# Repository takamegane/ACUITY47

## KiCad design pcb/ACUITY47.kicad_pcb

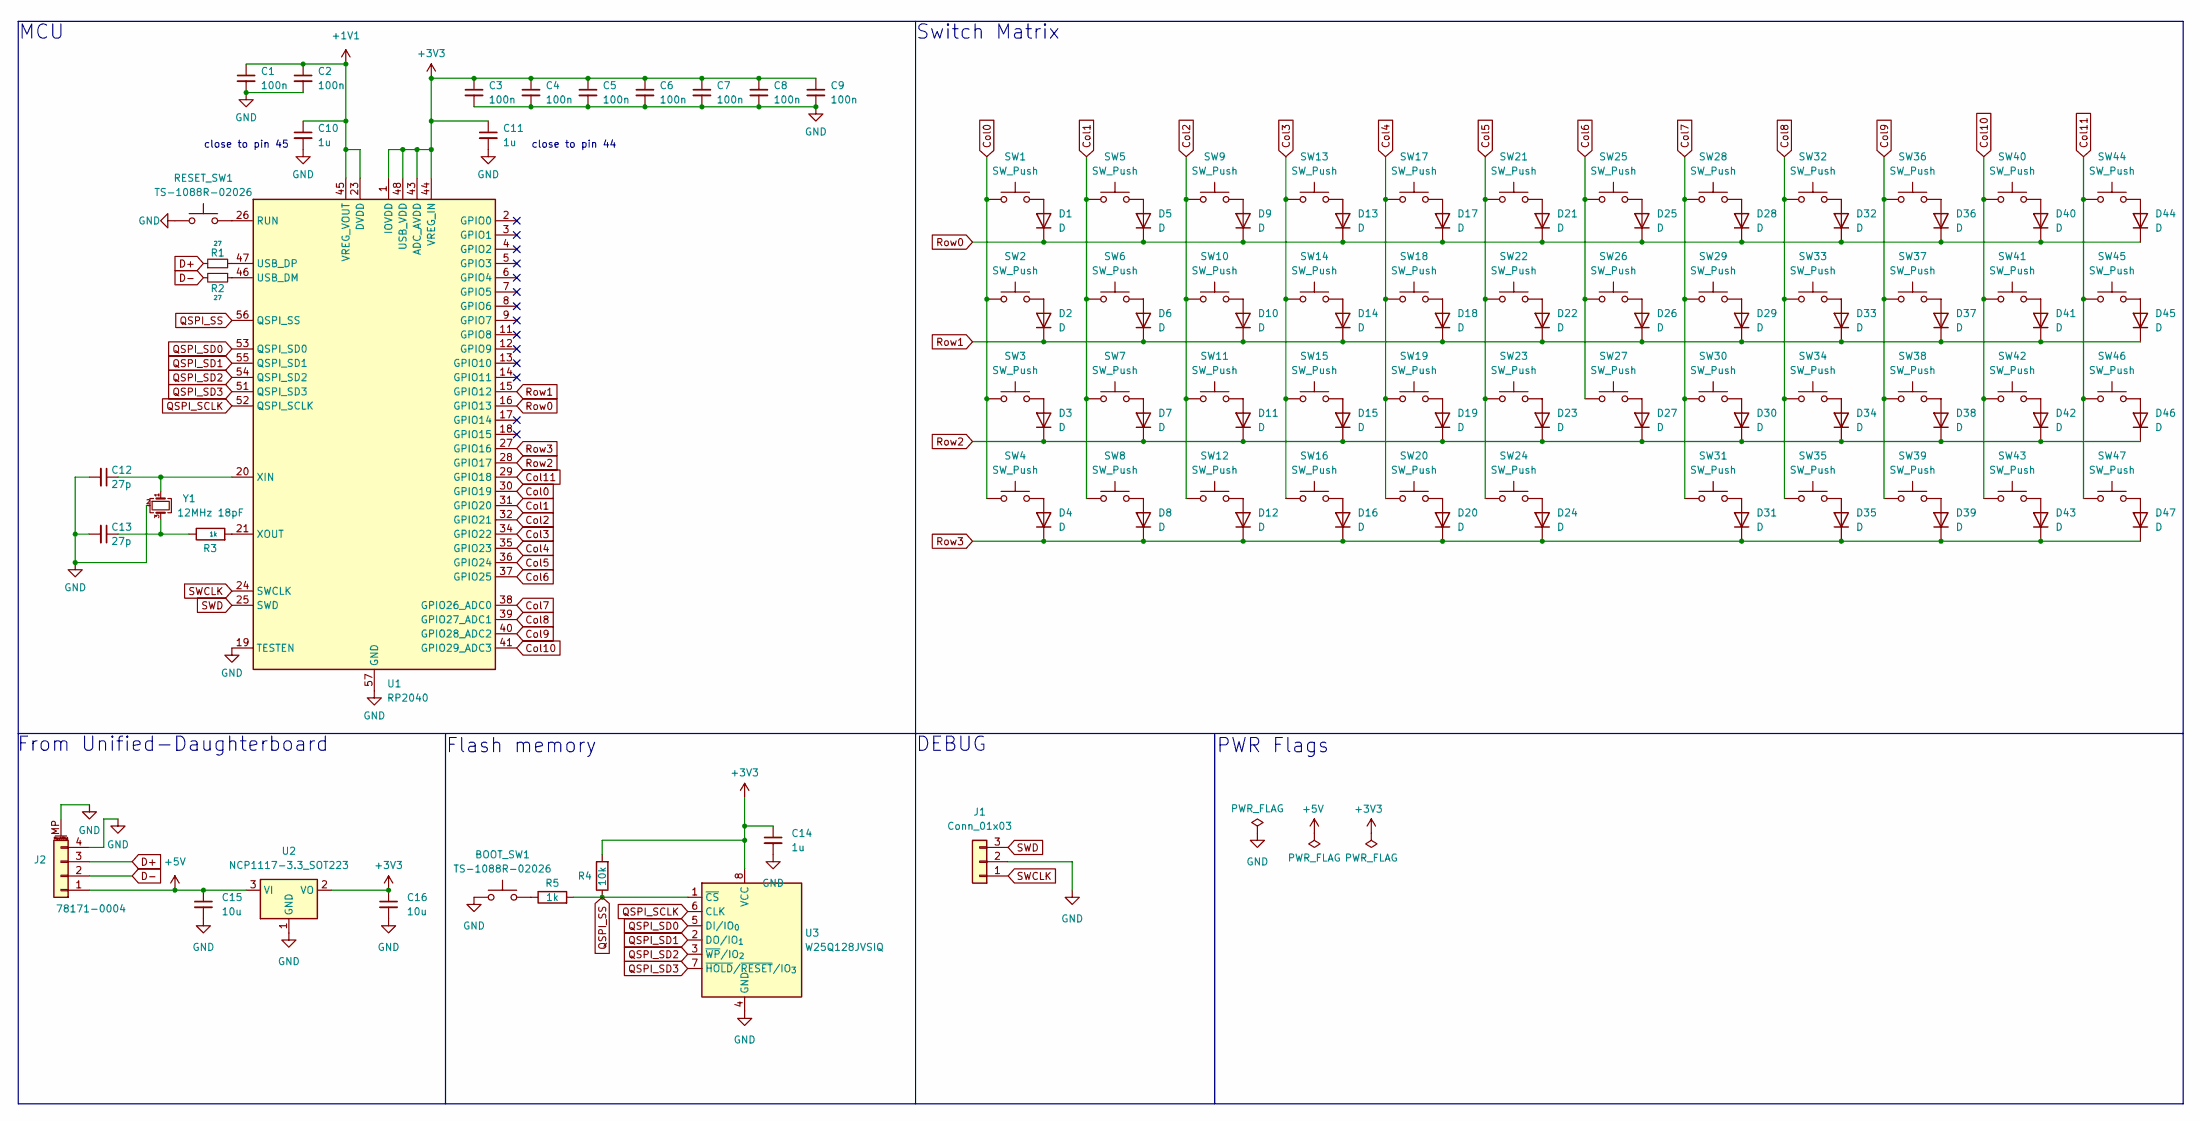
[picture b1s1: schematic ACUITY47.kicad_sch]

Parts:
BOOT_SW1: TS-1088R-02026; JLCPCB Part # C455280
C1, C2, C3, C4, C5, C6, C7, C8, C9: 100n; C_0402_1005Metric; JLCPCB Part # C1525
C10, C11, C14: 1u; C_0402_1005Metric; JLCPCB Part # C52923
C12, C13: 27p; C_0402_1005Metric; JLCPCB Part # C1557
C15, C16: 10u; C_0402_1005Metric; JLCPCB Part # C15525
D1, D2, D3, D4, D5, D6, D7, D8, D9, D10, D11, D12, D13, D14, D15, D16, D17, D18, D19, D20, D21, D22, D23, D24, D25, D26, D27, D28, D29, D30, D31, D32, D33, D34, D35, D36, D37, D38, D39, D40, D41, D42, D43, D44, D45, D46, D47: D; D_SOD-523; JLCPCB Part # C232841
J1: Conn_01x03; PinHeader_1x03_P2.54mm_Vertical
J2: 78171-0004; Pico-EZmate_PCB_Header; JLCPCB Part # C588524
R1, R2: 27; R_0402_1005Metric; JLCPCB Part # C2909343
R3, R5: 1k; R_0402_1005Metric; JLCPCB Part # C11702
R4: 10k; R_0402_1005Metric; JLCPCB Part # C25744
RESET_SW1: TS-1088R-02026; JLCPCB Part # C455280
SW1, SW2, SW3, SW4, SW5, SW6, SW7, SW8, SW9, SW10, SW11, SW12, SW13, SW14, SW15, SW16, SW17, SW18, SW19, SW20, SW21, SW22, SW23, SW25, SW26, SW27, SW28, SW29, SW30, SW31, SW32, SW33, SW34, SW35, SW36, SW37, SW38, SW39, SW40, SW41, SW42, SW43, SW44, SW45, SW46, SW47: SW_Push; MX_Hotswap_1U; JLCPCB Part # C49352235
SW24: SW_Push; MX_Hotswap_2U_Reverse; JLCPCB Part # C49352235
U1: RP2040; QFN-56-1EP_7x7mm_P0.4mm_EP3.2x3.2mm; JLCPCB Part # C2040
U2: NCP1117-3.3_SOT223; SOT-223-3_TabPin2; JLCPCB Part # C146799
U3: W25Q128JVSIQ; SOIC-8_5.3x5.3mm_P1.27mm; JLCPCB Part # C97521
Y1: 12MHz 18pF; Crystal_SMD_3225-4Pin_3.2x2.5mm; MFR.Part # Q22FA23V0041800; JLCPCB Part # C91749

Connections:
+1V1: C1.1, C2.1, C10.1, U1.23 (DVDD), U1.45 (VREG_VOUT), U1.50 (DVDD)
+3V3: C3.1, C4.1, C5.1, C6.1, C7.1, C8.1, C9.1, C11.1, C14.1, C16.1, R4.2, U1.1 (IOVDD), U1.10 (IOVDD), U1.22 (IOVDD), U1.33 (IOVDD), U1.42 (IOVDD), U1.43 (ADC_AVDD), U1.44 (VREG_IN), U1.48 (USB_VDD), U1.49 (IOVDD), U2.2 (VO), U3.8 (VCC)
+5V: C15.1, J2.1, U2.3 (VI)
Col0: SW1.1, SW2.1, SW3.1, SW4.1, U1.30 (GPIO19)
Col1: SW5.1, SW6.1, SW7.1, SW8.1, U1.31 (GPIO20)
Col2: SW9.1, SW10.1, SW11.1, SW12.1, U1.32 (GPIO21)
Col3: SW13.1, SW14.1, SW15.1, SW16.1, U1.34 (GPIO22)
Col4: SW17.1, SW18.1, SW19.1, SW20.1, U1.35 (GPIO23)
Col5: SW21.1, SW22.1, SW23.1, SW24.1, U1.36 (GPIO24)
Col6: SW25.1, SW26.1, SW27.1, U1.37 (GPIO25)
Col7: SW28.1, SW29.1, SW30.1, SW31.1, U1.38 (GPIO26_ADC0)
Col8: SW32.1, SW33.1, SW34.1, SW35.1, U1.39 (GPIO27_ADC1)
Col9: SW36.1, SW37.1, SW38.1, SW39.1, U1.40 (GPIO28_ADC2)
Col10: SW40.1, SW41.1, SW42.1, SW43.1, U1.41 (GPIO29_ADC3)
Col11: SW44.1, SW45.1, SW46.1, SW47.1, U1.29 (GPIO18)
D+: J2.3, R1.1
D-: J2.2, R2.2
GND: BOOT_SW1.1, C1.2, C2.2, C3.2, C4.2, C5.2, C6.2, C7.2, C8.2, C9.2, C10.2, C11.2, C12.2, C13.2, C14.2, C15.2, C16.2, J1.2, J2.4, J2.MP (MountPin), RESET_SW1.1, U1.19 (TESTEN), U1.57 (GND), U2.1 (GND), U3.4 (GND), Y1.2 (G), Y1.4 (G)
unnamed: BOOT_SW1.2, R5.1
unnamed: C13.1, R3.1, Y1.3
unnamed: D1.2 (A), SW1.2
unnamed: D2.2 (A), SW2.2
unnamed: D3.2 (A), SW3.2
unnamed: D4.2 (A), SW4.2
unnamed: D5.2 (A), SW5.2
unnamed: D6.2 (A), SW6.2
unnamed: D7.2 (A), SW7.2
unnamed: D8.2 (A), SW8.2
unnamed: D9.2 (A), SW9.2
unnamed: D10.2 (A), SW10.2
unnamed: D11.2 (A), SW11.2
unnamed: D12.2 (A), SW12.2
unnamed: D13.2 (A), SW13.2
unnamed: D14.2 (A), SW14.2
unnamed: D15.2 (A), SW15.2
unnamed: D16.2 (A), SW16.2
unnamed: D17.2 (A), SW17.2
unnamed: D18.2 (A), SW18.2
unnamed: D19.2 (A), SW19.2
unnamed: D20.2 (A), SW20.2
unnamed: D21.2 (A), SW21.2
unnamed: D22.2 (A), SW22.2
unnamed: D23.2 (A), SW23.2
unnamed: D24.2 (A), SW24.2
unnamed: D25.2 (A), SW25.2
unnamed: D26.2 (A), SW26.2
unnamed: D27.2 (A), SW27.2
unnamed: D28.2 (A), SW28.2
unnamed: D29.2 (A), SW29.2
unnamed: D30.2 (A), SW30.2
unnamed: D31.2 (A), SW31.2
unnamed: D32.2 (A), SW32.2
unnamed: D33.2 (A), SW33.2
unnamed: D34.2 (A), SW34.2
unnamed: D35.2 (A), SW35.2
unnamed: D36.2 (A), SW36.2
unnamed: D37.2 (A), SW37.2
unnamed: D38.2 (A), SW38.2
unnamed: D39.2 (A), SW39.2
unnamed: D40.2 (A), SW40.2
unnamed: D41.2 (A), SW41.2
unnamed: D42.2 (A), SW42.2
unnamed: D43.2 (A), SW43.2
unnamed: D44.2 (A), SW44.2
unnamed: D45.2 (A), SW45.2
unnamed: D46.2 (A), SW46.2
unnamed: D47.2 (A), SW47.2
unnamed: RESET_SW1.2, U1.26 (RUN)
unnamed: R2.1, U1.46 (USB_DM)
unnamed: R1.2, U1.47 (USB_DP)
unnamed: C12.1, U1.20 (XIN), Y1.1
unnamed: R3.2, U1.21 (XOUT)
QSPI_SCLK: U1.52 (QSPI_SCLK), U3.6 (CLK)
QSPI_SD0: U1.53 (QSPI_SD0), U3.5 (DI/IO_{0})
QSPI_SD1: U1.55 (QSPI_SD1), U3.2 (DO/IO_{1})
QSPI_SD2: U1.54 (QSPI_SD2), U3.3 (~WP/IO_{2})
QSPI_SD3: U1.51 (QSPI_SD3), U3.7 (~HOLD/~RESET/IO_{3})
QSPI_SS: R4.1, R5.2, U1.56 (QSPI_SS), U3.1 (~CS)
Row0: D1.1 (K), D5.1 (K), D9.1 (K), D13.1 (K), D17.1 (K), D21.1 (K), D25.1 (K), D28.1 (K), D32.1 (K), D36.1 (K), D40.1 (K), D44.1 (K), U1.16 (GPIO13)
Row1: D2.1 (K), D6.1 (K), D10.1 (K), D14.1 (K), D18.1 (K), D22.1 (K), D26.1 (K), D29.1 (K), D33.1 (K), D37.1 (K), D41.1 (K), D45.1 (K), U1.15 (GPIO12)
Row2: D3.1 (K), D7.1 (K), D11.1 (K), D15.1 (K), D19.1 (K), D23.1 (K), D27.1 (K), D30.1 (K), D34.1 (K), D38.1 (K), D42.1 (K), D46.1 (K), U1.28 (GPIO17)
Row3: D4.1 (K), D8.1 (K), D12.1 (K), D16.1 (K), D20.1 (K), D24.1 (K), D31.1 (K), D35.1 (K), D39.1 (K), D43.1 (K), D47.1 (K), U1.27 (GPIO16)
SWCLK: J1.1, U1.24 (SWCLK)
SWD: J1.3, U1.25 (SWD)

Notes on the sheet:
close to pin 44
DEBUG
close to pin 45
Flash memory
From Unified-Daughterboard
Switch Matrix
MCU
PWR Flags

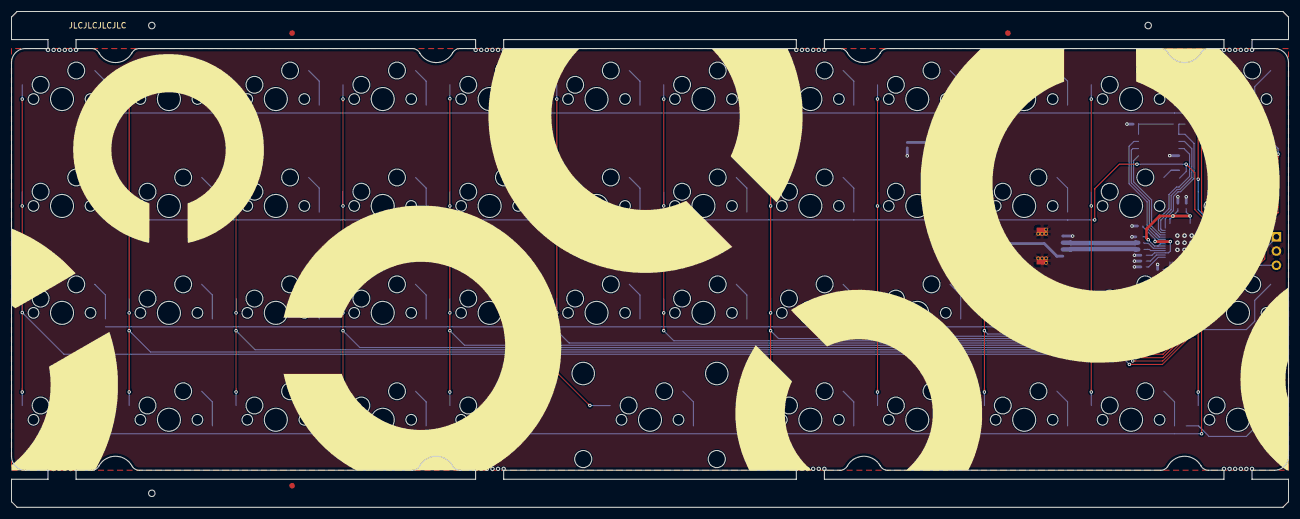
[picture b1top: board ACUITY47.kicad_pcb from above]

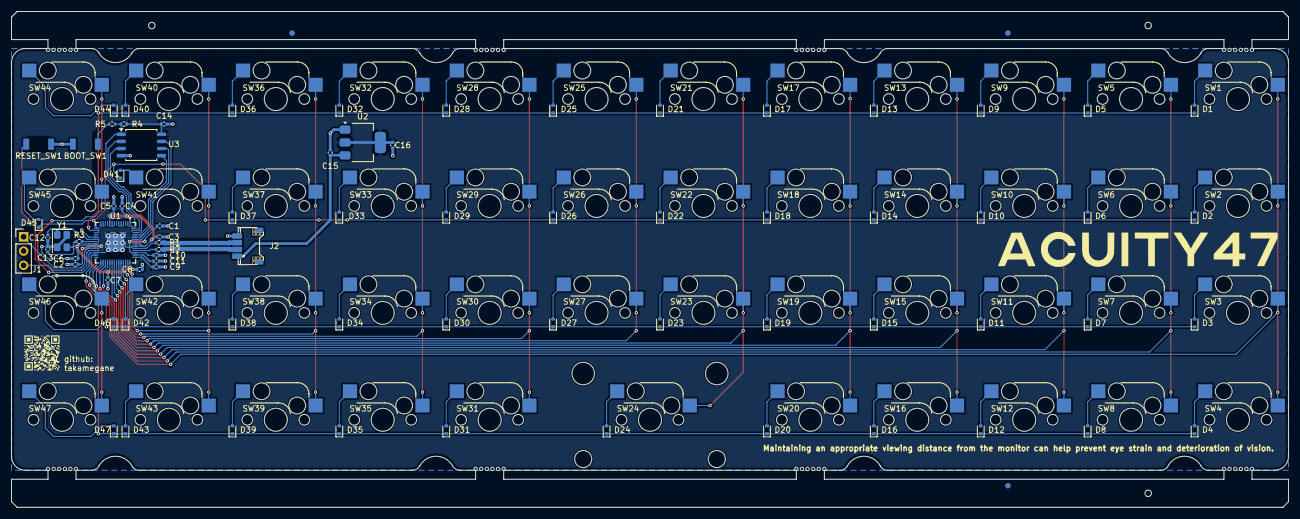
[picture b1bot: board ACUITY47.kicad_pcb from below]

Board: 2 copper layers, 227.5 x 88.3 mm, 180 parts (79 on the bottom side), 84 nets.

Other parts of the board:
KiKit_FID_B_1, KiKit_FID_B_2, KiKit_FID_B_3: Fiducial
KiKit_FID_T_1, KiKit_FID_T_2, KiKit_FID_T_3: Fiducial
KiKit_MB_1_1, KiKit_MB_1_2, KiKit_MB_1_3, KiKit_MB_1_4, KiKit_MB_1_5, KiKit_MB_1_6, KiKit_MB_2_1, KiKit_MB_2_2, KiKit_MB_2_3, KiKit_MB_2_4, KiKit_MB_2_5, KiKit_MB_2_6, KiKit_MB_3_1, KiKit_MB_3_2, KiKit_MB_3_3, KiKit_MB_3_4, KiKit_MB_3_5, KiKit_MB_3_6, KiKit_MB_4_1, KiKit_MB_4_2, KiKit_MB_4_3, KiKit_MB_4_4, KiKit_MB_4_5, KiKit_MB_4_6, KiKit_MB_5_1, KiKit_MB_5_2, KiKit_MB_5_3, KiKit_MB_5_4, KiKit_MB_5_5, KiKit_MB_5_6, KiKit_MB_6_1, KiKit_MB_6_2, KiKit_MB_6_3, KiKit_MB_6_4, KiKit_MB_6_5, KiKit_MB_6_6, KiKit_MB_7_1, KiKit_MB_7_2, KiKit_MB_7_3, KiKit_MB_7_4, KiKit_MB_7_5, KiKit_MB_7_6, KiKit_MB_8_1, KiKit_MB_8_2, KiKit_MB_8_3, KiKit_MB_8_4, KiKit_MB_8_5, KiKit_MB_8_6: NPTH
KiKit_TO_1, KiKit_TO_2, KiKit_TO_3: NPTH

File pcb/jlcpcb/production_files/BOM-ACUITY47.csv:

Comment,Designator,Footprint,LCSC,Quantity
100n,"C1,C2,C3,C4,C5,C6,C7,C8,C9",C_0402_1005Metric,C1525,9
10k,R4,R_0402_1005Metric,C25744,1
10u,"C15,C16",C_0402_1005Metric,C15525,2
12MHz 18pF,Y1,Crystal_SMD_3225-4Pin_3.2x2.5mm,C91749,1
1k,"R3,R5",R_0402_1005Metric,C11702,2
1u,"C10,C11,C14",C_0402_1005Metric,C52923,3
27,"R1,R2",R_0402_1005Metric,C2909343,2
27p,"C12,C13",C_0402_1005Metric,C1557,2
78171-0004,J2,Pico-EZmate_PCB_Header,C588524,1
D,"D1,D10,D11,D12,D13,D14,D15,D16,D17,D18,D19,D2,D20,D21,D22,D23,D24,D25,D26,D27,D28,D29,D3,D30,D31,D32,D33,D34,D35,D36,D37,D38,D39,D4,D40,D41,D42,D43,D44,D45,D46,D47,D5,D6,D7,D8,D9",D_SOD-523,C232841,47
NCP1117-3.3_SOT223,U2,SOT-223-3_TabPin2,C146799,1
RP2040,U1,QFN-56-1EP_7x7mm_P0.4mm_EP3.2x3.2mm,C2040,1
SW_Push,"SW1,SW10,SW11,SW12,SW13,SW14,SW15,SW16,SW17,SW18,SW19,SW2,SW20,SW21,SW22,SW23,SW24,SW25,SW26,SW27,SW28,SW29,SW3,SW30,SW31,SW32,SW33,SW34,SW35,SW36,SW37,SW38,SW39,SW4,SW40,SW41,SW42,SW43,SW44,SW45,SW46,SW47,SW5,SW6,SW7,SW8,SW9",MX_Hotswap_1U,C49352235,47
TS-1088R-02026,"BOOT_SW1,RESET_SW1",TS-1088R-02026,C455280,2
W25Q128JVSIQ,U3,SOIC-8_5.3x5.3mm_P1.27mm,C97521,1
